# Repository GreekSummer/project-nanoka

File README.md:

# project-nanoka

Project Nanoka is a Raspberry Pi Pico based audio output/input PCB. It exposes two audio terminals (input and output) as well as seven general-purposes input/output lines for external control. 

The PCB can be powered either through the Raspberry Pi's USB port, or through the power terminal. This requires a power module (also hosted on GitHub).

Right now, this is a prototype, and it's usefulness likely applies only to me. There are better solutions out there. I mainly created this to learn KiCad, and more broadly, PCB design which was always an interest of mine. This PCB should not be reproduced for your own personal use. If you do use it, **all responsibility is yours**. 

Known issues from previous version:
1. No audio output because the buffer chip is wired incorrectly (Input to A1, output to Y2)
2. Audio relay footprint is wrong
3. Audio relay footprint was accidentally flipped to the back of the board
4. C3 and C5 footprints are wrong
5. Audio input/output terminals are labelled in reverse
6. A potentiometer to adjust audio levels exists, but adjusting it below 220 ohms can cause damage to the Raspberry Pi

Fixed issues:
1. Audio is now properly routed from the buffer's A2 to Y2
2. Both relay issues have been fixed
3. Audio input/output terminals are labelled correctly and more clearly
4. C3 and C5 footprints fixed
5. Replaced potentiometer with a 220 ohm resistor

Improvements:
1. Replaced transistors with cheaper, more readily available ones
2. Tweaked transistor base resistor to draw less power from GPIO
4. Switched from a 4-layer setup to a 2-layer setup, making this cheaper to produce
5. Moved terminals closer to each other
6. General layout improvements
7. Symbols, footprints and 3D models are now packed in the repository

Ideas for the future:
1. Use a muxer IC to mix audio.
2. Switch from PWM audio to I2C audio for a cleaner signal.
3. Maybe re-design with SMD components to make this signafinantly smaller and elegant (but the THT components make it easier to assemble).

I have not yet re-produced this, so functionality and issues are unknown for this version.

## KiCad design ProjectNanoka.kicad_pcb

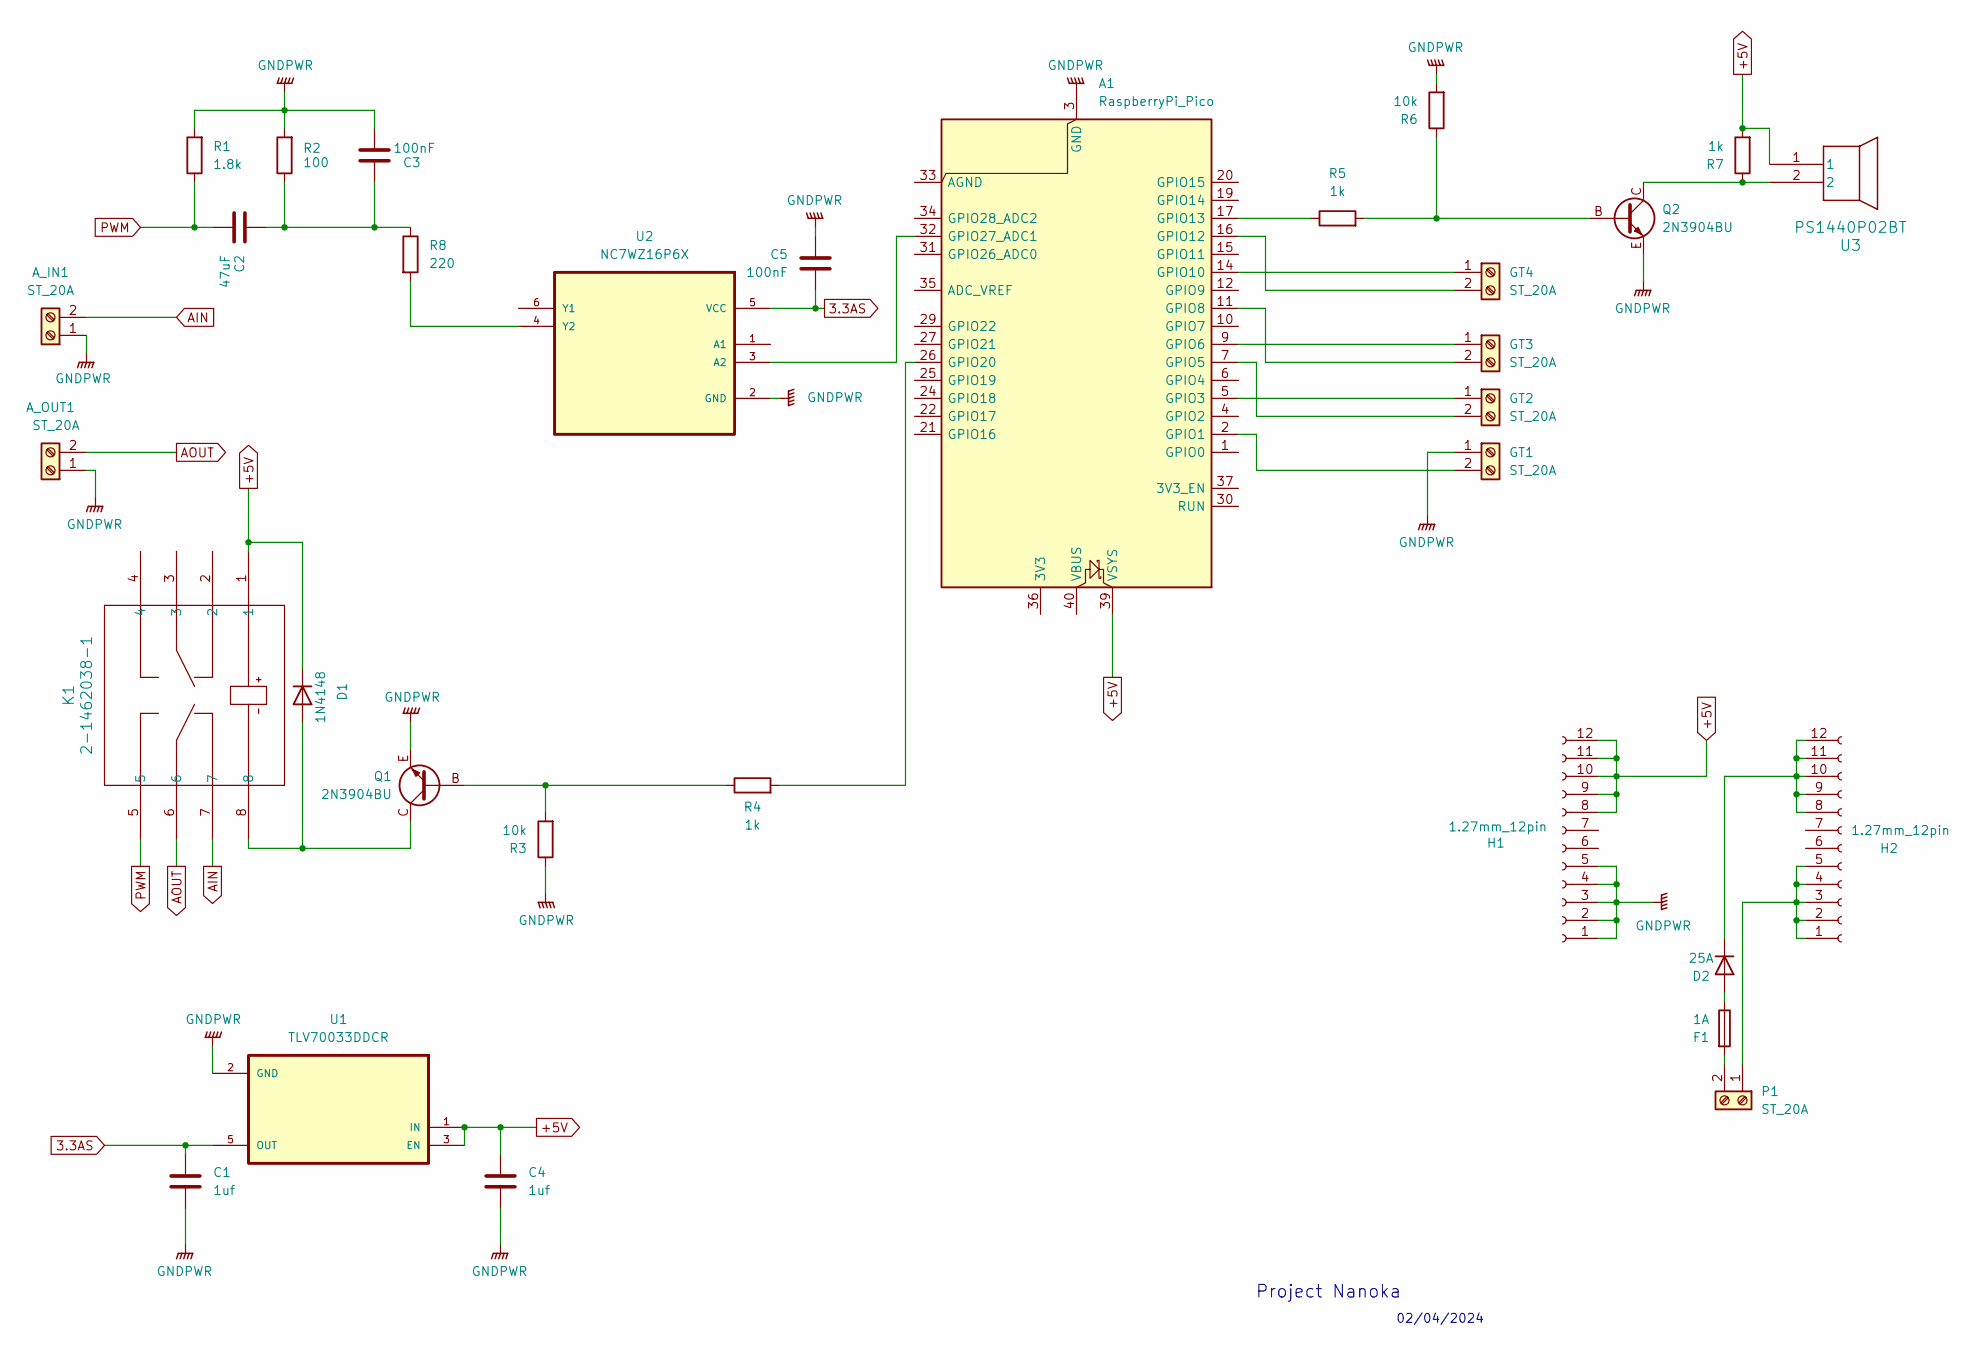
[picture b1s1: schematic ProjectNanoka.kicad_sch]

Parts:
A1: RaspberryPi_Pico; RPi_Pico_SMD_TH
A_IN1: ST_20A; CONN_1935161_PXC
A_OUT1: ST_20A; CONN_1935161_PXC
C1, C4: 1uf; CAP_C330C_MR_X7R_KEM
C2: 47uF; CAP_UUQ_5X5P4_NCH
C3, C5: 100nF; CAP_C320_KEM
D1: 1N4148; D_DO-35_SOD27_P7.62mm_Horizontal
D2: 25A; P33_D5.4x7.5
F1: 1A; 20x300_FUSE_HOLDER_0PTF0078P_LTF
GT1, GT2, GT3, GT4: ST_20A; CONN_1935161_PXC
H1, H2: 1.27mm_12pin; PinHeader_1x12_P1.27mm_Vertical_Modded
K1: 2-1462038-1; RELAY8-TH_NON-LATCH_1-COIL
P1: ST_20A; CONN_1935161_PXC
Q1, Q2: 2N3904BU
R1: 1.8k; STA_CF14_STP
R2: 100; STA_CF14_STP
R3, R6: 10k; STA_RNF14_STP
R4, R5, R7: 1k; STA_RNF14_STP
R8: 220; STA_RNMF14_STP
U1: TLV70033DDCR; SOT95P280X110-5N
U2: NC7WZ16P6X; SOT65P210X110-6N; MPN NC7WZ16P6X
U3: PS1440P02BT; PS1440P02BT_TDK

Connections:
3.3AS: C1.1, C5.1, U1.5 (OUT), U2.5 (VCC)
+5V: A1.39 (VSYS), C4.1, D1.1 (K), H1.8, H1.9, H1.10, H1.11, H1.12, K1.1, R7.2, U1.1 (IN), U1.3 (EN), U3.1
AIN: A_IN1.2, K1.7
AOUT: A_OUT1.2, K1.6
GNDPWR: A1.3 (GND), A1.8 (GND), A1.13 (GND), A1.18 (GND), A1.23 (GND), A1.28 (GND), A1.38 (GND), A_IN1.1, A_OUT1.1, C1.2, C3.2, C4.2, C5.2, GT1.1, H1.1, H1.2, H1.3, H1.4, H1.5, Q1.E, Q2.E, R1.2, R2.2, R3.1, R6.2, U1.2 (GND), U2.2 (GND)
unnamed: A1.2 (GPIO1), GT1.2
unnamed: A1.5 (GPIO3), GT2.1
unnamed: A1.7 (GPIO5), GT2.2
unnamed: A1.9 (GPIO6), GT3.1
unnamed: A1.11 (GPIO8), GT3.2
unnamed: A1.14 (GPIO10), GT4.1
unnamed: A1.16 (GPIO12), GT4.2
unnamed: A1.17 (GPIO13), R5.1
unnamed: A1.26 (GPIO20), R4.2
unnamed: A1.32 (GPIO27_ADC1), U2.3 (A2)
unnamed: C2.1, C3.1, R2.1, R8.1
unnamed: D1.2 (A), K1.8, Q1.C
unnamed: D2.2 (A), F1.1
unnamed: D2.1 (K), H2.8, H2.9, H2.10, H2.11, H2.12
unnamed: H2.1, H2.2, H2.3, H2.4, H2.5, P1.1
unnamed: F1.2, P1.2
unnamed: Q1.B, R3.2, R4.1
unnamed: Q2.B, R5.2, R6.1
unnamed: Q2.C, R7.1, U3.2
unnamed: R8.2, U2.4 (Y2)
PWM: C2.2, K1.5, R1.1

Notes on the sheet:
Project Nanoka
02/04/2024

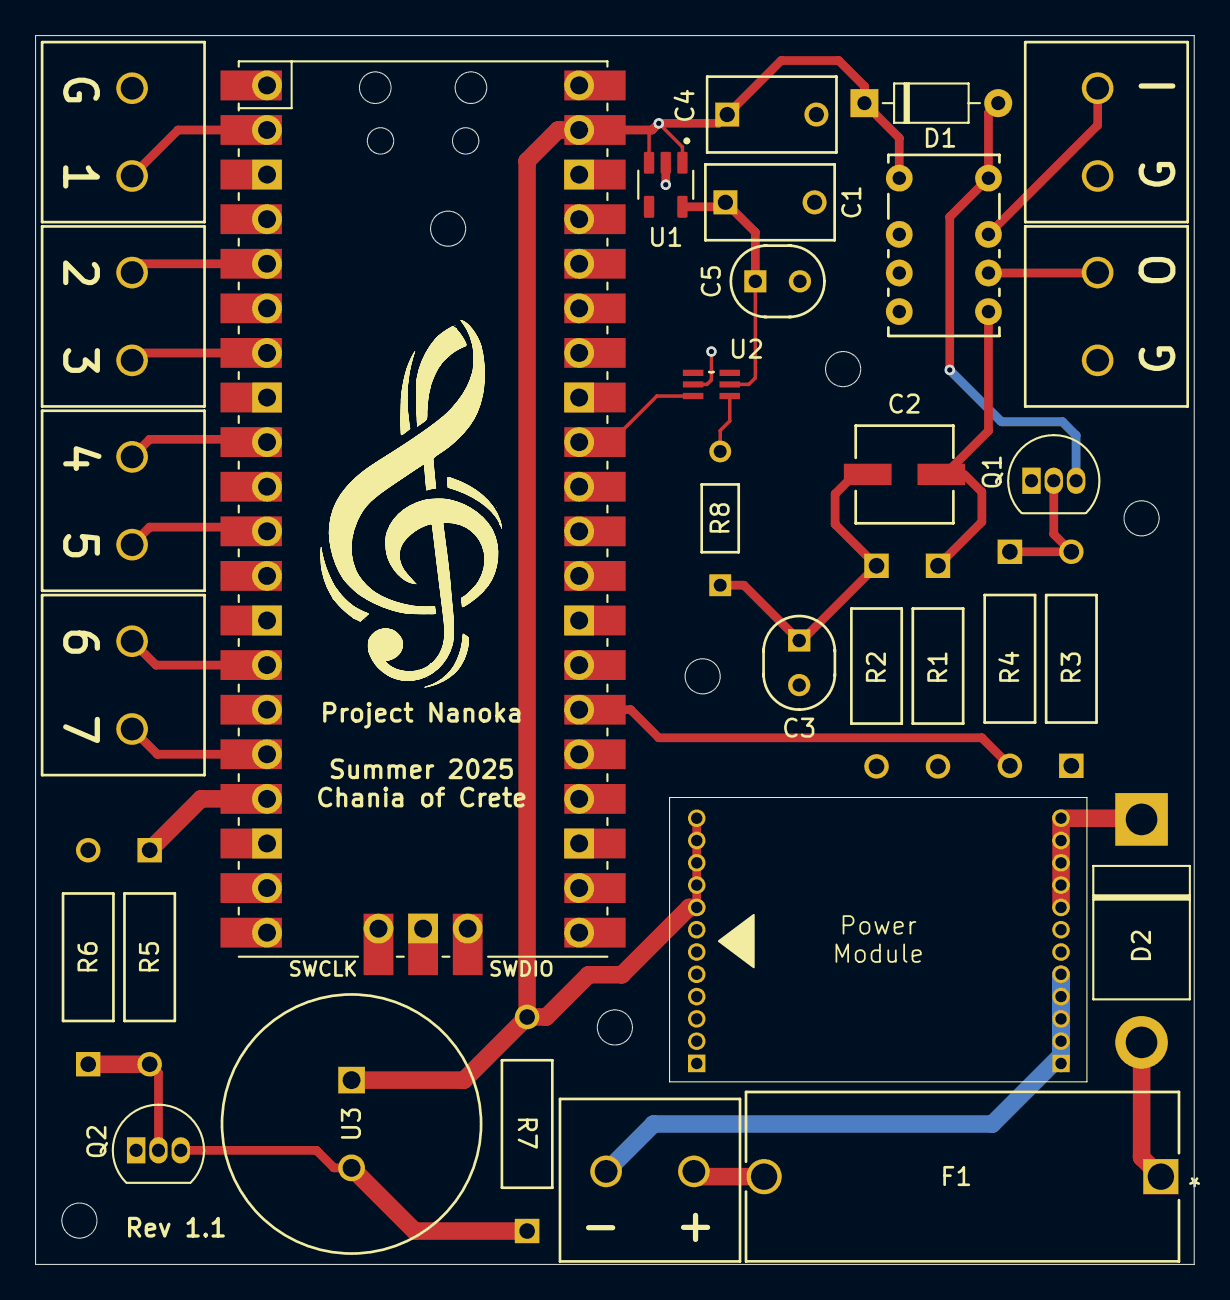
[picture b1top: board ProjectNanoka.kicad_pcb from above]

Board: 2 copper layers, 66.0 x 70.0 mm, 32 parts (0 on the bottom side), 26 nets.

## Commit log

2025-08-02 Add files
2025-08-02 Add images and update README
2025-08-02 Modify README
2025-08-02 Rename 3d-render to 3d-render.png
2025-08-13 Remove locks
2025-08-13 Fix issues found in v1
2025-08-13 Make improvements to board
2025-08-13 Embed libraries and 3d models
2025-08-14 Replaced 2SC1815 with 2N3904BU
2025-08-14 Replaced RV1 with a 220ohm resistor
2025-08-14 Add DigiKey BOM
2025-08-14 Updated readme info
